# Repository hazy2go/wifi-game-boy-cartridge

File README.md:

# WiFi Game Boy Cartridge (Rev B)

A WiFi cartridge for the original Game Boy and the Game Boy Color that **can't brown out the console**.
An RP2350 serves the whole cartridge bus, and an ESP32-C3 radio sits behind a power stage. That stage limits what the cart takes from the console to a steady 150 mA and never pulls the console's 5 V rail below 4.588 V.
Fully assembled by JLCPCB, nothing to hand-solder. Designed by Hazy, co-created with RemAI.

| | |
|---|---|
| Status (2026-10-16) | Hardware design finished, all checks green, JLC order files ready, **not ordered yet**. Bench tests on a XIAO ESP32C3 dev board are under way: RF calibration (about 30 ms at about 60 mA, looks OK), antenna (strong) and the radio app on real WiFi (all commands work) are done; the Pico 2 link test and a power-model update with the measured numbers come next. See `docs/LOGBOOK.md`. |
| Board | 6 layers, 0.8 mm, standard cartridge shell, USB-C |
| Cartridge core | RP2350B + 8 MB HyperRAM + 16 MB flash + microSD + RTC, serving the cartridge bus over PIO (the proven Croco Cartridge design) |
| Radio | ESP32-C3-MINI-1U on the RP2350's SPI bus, stick-on FPC antenna (MHF III plug) inside the shell. Both chips flash over the one USB-C port (built-in USB hub) |
| Power | USB/console power mux → 150 mA current limit → precision input-voltage regulator (console never pulled below 4.588 V ±1 %) → ~1 mF reservoir → power-good → buck-boost to 3.3 V. The radio firmware admits every WiFi frame against the energy left in the reservoir |

## Why

Earlier WiFi carts powered the radio straight from the Game Boy's 5 V. Every transmit burst (170 to 350 mA) hit the console's weak power converter, and on tired batteries the whole system collapsed.
Here the console only ever sees a steady, limited draw. The bursts come out of a local reservoir, and if the console can't keep up, the radio waits instead of the Game Boy crashing.

| Top | Bottom |
|---|---|
|  |  |

## Proven before ordering

None of this has been built yet. Instead, everything was simulated against real part models and checked against the actual layout:
- **Power stage, at transistor level:** ngspice with TI and Vishay vendor models, covering hot-plug, bursts after idle, loop stability and every tolerance corner (`sim/power`, audits A1 to A8).
- **Full system:** a real Game Boy ROM runs in a cycle-accurate emulator and goes through the cartridge's mailbox. The models cover the RP2350, the ESP32-C3 running the *shipped* power-manager C code, and the power plant including the routed copper's resistance. Tested on fresh, tired and weak batteries (`sim/system`).
- **Layout:**
  - KiCad ERC, DRC and connectivity are clean against the Croco baseline (`verify/`).
  - Every part is checked pin by pin against the exact JLC part.
  - The placement file is derived from JLC's own footprints.

Demo ROM in that simulation: WiFi scan (real networks seen by the host), password entry, then a live BTC/USD chart:

## Repository

| Path | What |
|---|---|
| `CLAUDE.md` | Handoff: current status, rules, software to-do (start here) |
| `docs/ARCHITECTURE.md` | Block diagram, why each block, pin budget |
| `docs/LOGBOOK.md` | Every decision, check and result, in order |
| `hw/rev-b/` | KiCad project, layout tools, `fab/` order files (`fab/ORDER.md`) |
| `docs/ROM_DEV.md` | **Building ROMs for the cart:** mailbox, commands, timing, testing |
| `gb/gbdk/`, `gb/rgbds/` | WiFi libraries for C (GBDK-2020) and assembly (RGBDS), template, examples |
| `firmware/esp32c3/` | Radio firmware: app, power manager, link protocol, shared C components |
| `firmware/xiao/` | Bench tests for the dev board (calibration time, antenna, boot time) |
| `sim/power/`, `sim/system/` | Power-stage and full-system simulations (`run_rom.py` runs any ROM on the simulated cart) |
| `verify/` | Pre-order gates |
| `legacy/` | The original ESP8266 cartridge's code, PCB and shell, kept for reference only |

## Credits

- Designed by [hazy2go](https://github.com/hazy2go), co-created with RemAI (the avatar on the back of the board).
- Forked from [Staacks/wifi-game-boy-cartridge](https://github.com/Staacks/wifi-game-boy-cartridge) (there.oughta.be). The original ESP8266 cartridge was the idea and the starting point.
- The cartridge core is [Croco Cartridge V2.1](https://github.com/shilga/rp-gameboy-cartridge-hw) by shilga. Firmware base: [rp2350-gameboy-cartridge-firmware](https://github.com/shilga/rp2350-gameboy-cartridge-firmware).
- The emulator in the simulation is [Peanut-GB](https://github.com/deltabeard/Peanut-GB). The DMG power-supply analysis uses [Gekkio's gb-schematics](https://github.com/Gekkio/gb-schematics).

## License

| What | License |
|---|---|
| Hardware design (`hw/rev-b/`: schematic, board, fab files) | CERN-OHL-P v2, inherited from Croco Cartridge (`hw/rev-b/LICENSE-CERN-OHL-P.md`) |
| Everything else here: radio firmware (`firmware/`), Game Boy libraries and examples (`gb/`), simulators (`sim/`), gates (`verify/`), board tools (`hw/rev-b/tools/`), docs | **MIT** (`LICENSE`). Permissive on purpose: ROMs built with the libraries can use any license |
| RP2350 cart firmware ([hazy2go/rp2350-gameboy-cartridge-firmware](https://github.com/hazy2go/rp2350-gameboy-cartridge-firmware)) | GPL-3, as its upstream (Croco) |
| `sim/system/third_party/Peanut-GB` | MIT (one local fix, marked in the code) |
| `sim/system/rom/font8x8_basic.h` (test ROM font) | Public domain (Daniel Hepper, after the IBM VGA font) |
| Vendor SPICE models (TI, Vishay) | Not included: `sim/models/fetch_models.py` downloads them under the vendors' terms |
| `legacy/` | The original project's licenses: GPL-3 for code and PCB, CC-BY-NC-SA for the shell (`legacy/README.md`) |

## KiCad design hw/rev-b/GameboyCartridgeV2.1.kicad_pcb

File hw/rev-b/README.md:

# Rev B hardware

Status (2026-10-14): 6-layer 0.8 mm, all parts placed, fully routed and tidied, all gates green (see below). Not ordered yet.

Base: **Croco Cartridge V2.1** by shilga, imported unmodified from
https://github.com/shilga/rp-gameboy-cartridge-hw (`KiCad/V2/GameboyCartridgeV2.1`, commit cb750a1, 2025-11-29).
Licence of the imported design: CERN Open Hardware Licence v2 Permissive (`LICENSE-CERN-OHL-P.md`). All credit for the cartridge core goes to the Croco project.

This fork adds a WiFi radio (ESP32-C3) and a console-safe power stage on top of it. See `../../docs/ARCHITECTURE.md` and `../../docs/LOGBOOK.md`.

Rules for changes here:
- The first commit of this folder is the untouched upstream design, so every later diff is ours.
- Nothing is ordered until ERC/DRC are clean against an explicit JLC rule set, the power stage passes `sim/power`, the height/antenna checks in the logbook are closed, and the full-system simulation with a Game Boy ROM (`sim/system`) passes on the final layout. State 2026-10-14: all met; the order files still need Hazy's review.
- Gate commands: `python3 verify/kicad_check.py` (ERC/DRC/unconnected/parity vs Croco's baseline), `verify/jlc_check.py` (DRC at JLC's 6-layer limits), `verify/netlist_check.py`, `verify/sim_vs_netlist.py`, `verify/design_calcs.py`, `sim/system/run_system.py`, `sim/system/run_demo.py`.
- Layout tools used: `tools/` (placement, Freerouting import, finisher, pull-tight cleaner, audits, copper-resistance extraction). Each is documented at the top of the file.
- Croco's author recommends 0.8mm board thickness and ENIG finish.

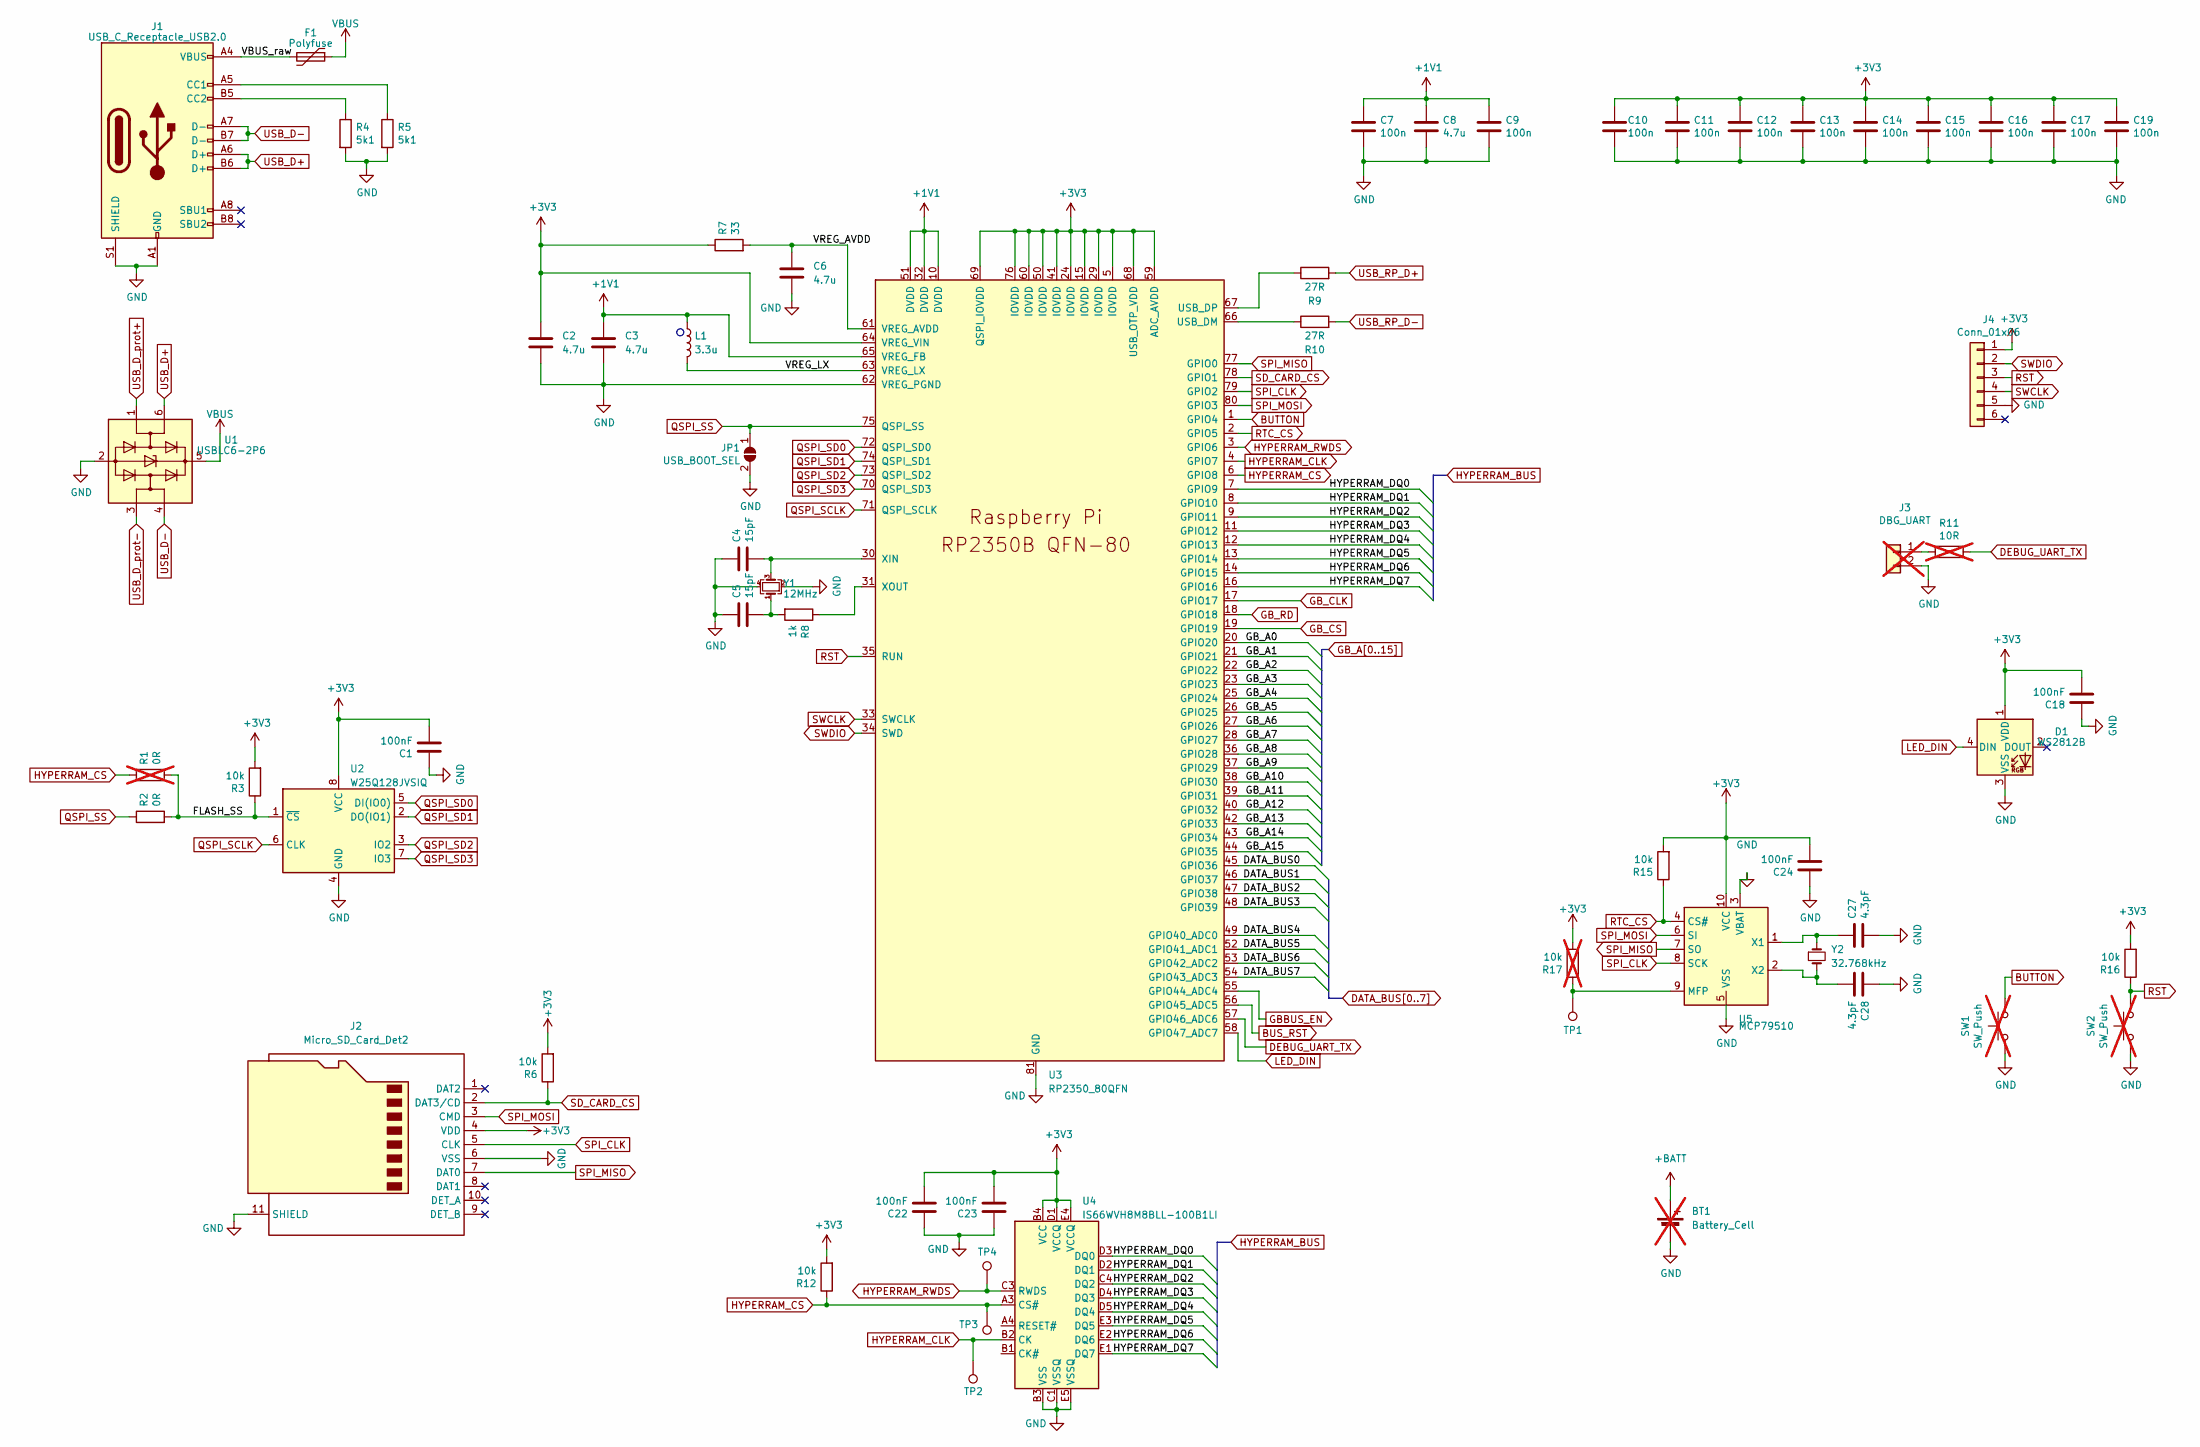
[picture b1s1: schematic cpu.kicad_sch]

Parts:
BT1: Battery_Cell; BatteryHolder_Keystone_3000_1x12mm; LCSC C6997853; not fitted
C1, C18, C22, C23, C24: 100nF; C_0603_1608Metric
C2, C3: 4.7u; C_0402_1005Metric_small_pads
C4, C5: 15pF; C_0603_1608Metric; LCSC C1644
C6, C8: 4.7u; C_0402_1005Metric
C7, C9, C10, C11, C12, C13, C14, C15, C16, C17, C19: 100n; C_0402_1005Metric
C27, C28: 4.3pF; C_0603_1608Metric; LCSC C59526
D1: WS2812B; LED_WS2812B_PLCC4_5.0x5.0mm_P3.2mm; LCSC C2761795
F1: Polyfuse; Fuse_1206_3216Metric; LCSC C2649911
J1: USB_C_Receptacle_USB2.0; USB_C_Receptacle_GCT_USB4105-xx-A_16P_TopMnt_Horizontal; LCSC C2927037
J2: Micro_SD_Card_Det2; microSD_HC_Hirose_DM3D-SF; LCSC C719027
J3: DBG_UART; PinHeader_1x02_P2.54mm_Horizontal; not fitted
J4: Conn_01x06; Tag-Connect_TC2030-IDC-NL_2x03_P1.27mm_Vertical
JP1: USB_BOOT_SEL; SolderJumper-2_P1.3mm_Open_RoundedPad1.0x1.5mm
L1: 3.3u; L_pol_2016; LCSC C42411119
R1: 0R; R_0603_1608Metric; not fitted
R2: 0R; R_0603_1608Metric
R3, R6, R12, R15, R16: 10k; R_0603_1608Metric
R4, R5: 5k1; R_0603_1608Metric
R7: 33; R_0402_1005Metric
R8: 1k; R_0603_1608Metric
R9, R10: 27R; R_0603_1608Metric
R11: 10R; R_0603_1608Metric; not fitted
R17: 10k; R_0603_1608Metric; not fitted
SW1: SW_Push; GameBoy_soft_button; not fitted
SW2: SW_Push; SW_SPST_PTS810; not fitted
TP1, TP2, TP3, TP4: TestPoint; TestPoint_Pad_D1.0mm
U1: USBLC6-2P6; SOT-666; LCSC C2827693
U2: W25Q128JVSIQ; SOIC-8_5.23x5.23mm_P1.27mm; LCSC C97521
U3: RP2350_80QFN; RP2350-QFN-80-1EP_10x10_P0.4mm_EP3.4x3.4mm_ThermalVias; LCSC C42415655
U4: IS66WVH8M8BLL-100B1LI; BGA25C100P5X5_800X600X120N; LCSC C1349096
U5: MCP79510; MSOP-10_3x3mm_P0.5mm; LCSC C627708
Y1: 12MHz; Crystal_SMD_TXC_7M-4Pin_3.2x2.5mm; LCSC C20625731
Y2: 32.768kHz; Crystal_SMD_TXC_9HT11-2Pin_2.0x1.2mm; LCSC C97602

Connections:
+1V1: C3.1, C7.1, C8.1, C9.1, L1.1, U3.10 (DVDD), U3.32 (DVDD), U3.51 (DVDD), U3.65 (VREG_FB)
+3V3: C1.2, C2.1, C10.1, C11.1, C12.1, C13.1, C14.1, C15.1, C16.1, C17.1, C18.2, C19.1, C22.2, C23.2, C24.2, D1.1 (VDD), J2.4 (VDD), J4.1, R3.2, R6.2, R7.1, R12.2, R15.2, R16.2, R17.2, U2.8 (VCC), U3.5 (IOVDD), U3.15 (IOVDD), U3.24 (IOVDD), U3.29 (IOVDD), U3.41 (IOVDD), U3.50 (IOVDD), U3.59 (ADC_AVDD), U3.60 (IOVDD), U3.64 (VREG_VIN), U3.68 (USB_OTP_VDD), U3.69 (QSPI_IOVDD), U3.76 (IOVDD), U4.B4 (VCC), U4.D1 (VCCQ), U4.E4 (VCCQ), U5.10 (VCC); also elsewhere on the board
/CPU/FLASH_SS: R1.2, R2.2, R3.1, U2.1 (~CS)
/CPU/HYPERRAM_DQ0: U3.7 (GPIO9), U4.D3 (DQ0)
/CPU/HYPERRAM_DQ1: U3.8 (GPIO10), U4.D2 (DQ1)
/CPU/HYPERRAM_DQ2: U3.9 (GPIO11), U4.C4 (DQ2)
/CPU/HYPERRAM_DQ3: U3.11 (GPIO12), U4.D4 (DQ3)
/CPU/HYPERRAM_DQ4: U3.12 (GPIO13), U4.D5 (DQ4)
/CPU/HYPERRAM_DQ5: U3.13 (GPIO14), U4.E3 (DQ5)
/CPU/HYPERRAM_DQ6: U3.14 (GPIO15), U4.E2 (DQ6)
/CPU/HYPERRAM_DQ7: U3.16 (GPIO16), U4.E1 (DQ7)
/CPU/VBUS_raw: F1.2, J1.A4 (VBUS), J1.A9 (VBUS), J1.B4 (VBUS), J1.B9 (VBUS)
/CPU/VREG_AVDD: C6.1, R7.2, U3.61 (VREG_AVDD)
/CPU/VREG_LX: L1.2, U3.63 (VREG_LX)
BUS_RST: U3.56 (GPIO45_ADC5); also elsewhere on the board
BUTTON: SW1.1, U3.1 (GPIO4)
DATA_BUS0: U3.45 (GPIO36); also elsewhere on the board
DATA_BUS1: U3.46 (GPIO37); also elsewhere on the board
DATA_BUS2: U3.47 (GPIO38); also elsewhere on the board
DATA_BUS3: U3.48 (GPIO39); also elsewhere on the board
DATA_BUS4: U3.49 (GPIO40_ADC0); also elsewhere on the board
DATA_BUS5: U3.52 (GPIO41_ADC1); also elsewhere on the board
DATA_BUS6: U3.53 (GPIO42_ADC2); also elsewhere on the board
DATA_BUS7: U3.54 (GPIO43_ADC3); also elsewhere on the board
DEBUG_UART_TX: R11.1, U3.57 (GPIO46_ADC6); also elsewhere on the board
GBBUS_EN: U3.55 (GPIO44_ADC4); also elsewhere on the board
GB_A0: U3.20 (GPIO20); also elsewhere on the board
GB_A1: U3.21 (GPIO21); also elsewhere on the board
GB_A2: U3.22 (GPIO22); also elsewhere on the board
GB_A3: U3.23 (GPIO23); also elsewhere on the board
GB_A4: U3.25 (GPIO24); also elsewhere on the board
GB_A5: U3.26 (GPIO25); also elsewhere on the board
GB_A6: U3.27 (GPIO26); also elsewhere on the board
GB_A7: U3.28 (GPIO27); also elsewhere on the board
GB_A8: U3.36 (GPIO28); also elsewhere on the board
GB_A9: U3.37 (GPIO29); also elsewhere on the board
GB_A10: U3.38 (GPIO30); also elsewhere on the board
GB_A11: U3.39 (GPIO31); also elsewhere on the board
GB_A12: U3.40 (GPIO32); also elsewhere on the board
GB_A13: U3.42 (GPIO33); also elsewhere on the board
GB_A14: U3.43 (GPIO34); also elsewhere on the board
GB_A15: U3.44 (GPIO35); also elsewhere on the board
GB_CLK: U3.17 (GPIO17); also elsewhere on the board
GB_CS: U3.19 (GPIO19); also elsewhere on the board
GB_RD: U3.18 (GPIO18); also elsewhere on the board
GND: BT1.2 (-), C1.1, C2.2, C3.2, C4.1, C5.1, C6.2, C7.2, C8.2, C9.2, C10.2, C11.2, C12.2, C13.2, C14.2, C15.2, C16.2, C17.2, C18.1, C19.2, C22.1, C23.1, C24.1, C27.2, C28.1, D1.3 (VSS), J1.A1 (GND), J1.A12 (GND), J1.B1 (GND), J1.B12 (GND), J1.S1 (SHIELD), J2.6 (VSS), J2.11 (SHIELD), J3.2, J4.5, JP1.2 (B), R4.2, R5.2, SW1.2, SW2.2, U1.2 (GND), U2.4 (GND), U3.62 (VREG_PGND), U3.81 (GND), U4.B3 (VSS), U4.C1 (VSSQ), U4.E5 (VSSQ), U5.3 (VBAT), U5.5 (VSS), Y1.2, Y1.4; also elsewhere on the board
HYPERRAM_CLK: TP2.1, U3.4 (GPIO7), U4.B2 (CK)
HYPERRAM_CS: R1.1, R12.1, TP3.1, U3.6 (GPIO8), U4.A3 (CS#)
HYPERRAM_RWDS: TP4.1, U3.3 (GPIO6), U4.C3 (RWDS)
LED_DIN: D1.4 (DIN), U3.58 (GPIO47_ADC7)
unnamed: C5.2, R8.2, Y1.1
unnamed: J1.A5 (CC1), R5.1
unnamed: J1.B5 (CC2), R4.1
unnamed: J3.1, R11.2
unnamed: R10.1, U3.66 (USB_DM)
unnamed: R9.1, U3.67 (USB_DP)
unnamed: C4.2, U3.30 (XIN), Y1.3
unnamed: R8.1, U3.31 (XOUT)
unnamed: R17.1, TP1.1, U5.9 (MFP)
unnamed: C27.1, U5.1 (X1), Y2.1
unnamed: C28.2, U5.2 (X2), Y2.2
QSPI_SCLK: U2.6 (CLK), U3.71 (QSPI_SCLK)
QSPI_SD0: U2.5 (DI(IO0)), U3.72 (QSPI_SD0)
QSPI_SD1: U2.2 (DO(IO1)), U3.74 (QSPI_SD1)
QSPI_SD2: U2.3 (IO2), U3.73 (QSPI_SD2)
QSPI_SD3: U2.7 (IO3), U3.70 (QSPI_SD3)
QSPI_SS: JP1.1 (A), R2.1, U3.75 (QSPI_SS)
RST: J4.3, R16.1, SW2.1, U3.35 (RUN)
RTC_CS: R15.1, U3.2 (GPIO5), U5.4 (CS#)
SD_CARD_CS: J2.2 (DAT3/CD), R6.1, U3.78 (GPIO1)
SPI_CLK: J2.5 (CLK), U3.79 (GPIO2), U5.8 (SCK); also elsewhere on the board
SPI_MISO: J2.7 (DAT0), U3.77 (GPIO0), U5.7 (SO); also elsewhere on the board
SPI_MOSI: J2.3 (CMD), U3.80 (GPIO3), U5.6 (SI); also elsewhere on the board
SWCLK: J4.4, U3.33 (SWCLK)
SWDIO: J4.2, U3.34 (SWD)
USB_D+: J1.A6 (D+), J1.B6 (D+), U1.6 (I/O1)
USB_D-: J1.A7 (D-), J1.B7 (D-), U1.4 (I/O2)
USB_D_prot+: U1.1 (I/O1); also elsewhere on the board
USB_D_prot-: U1.3 (I/O2); also elsewhere on the board
USB_RP_D+: R9.2; also elsewhere on the board
USB_RP_D-: R10.2; also elsewhere on the board
VBUS: F1.1, U1.5 (VBUS); also elsewhere on the board

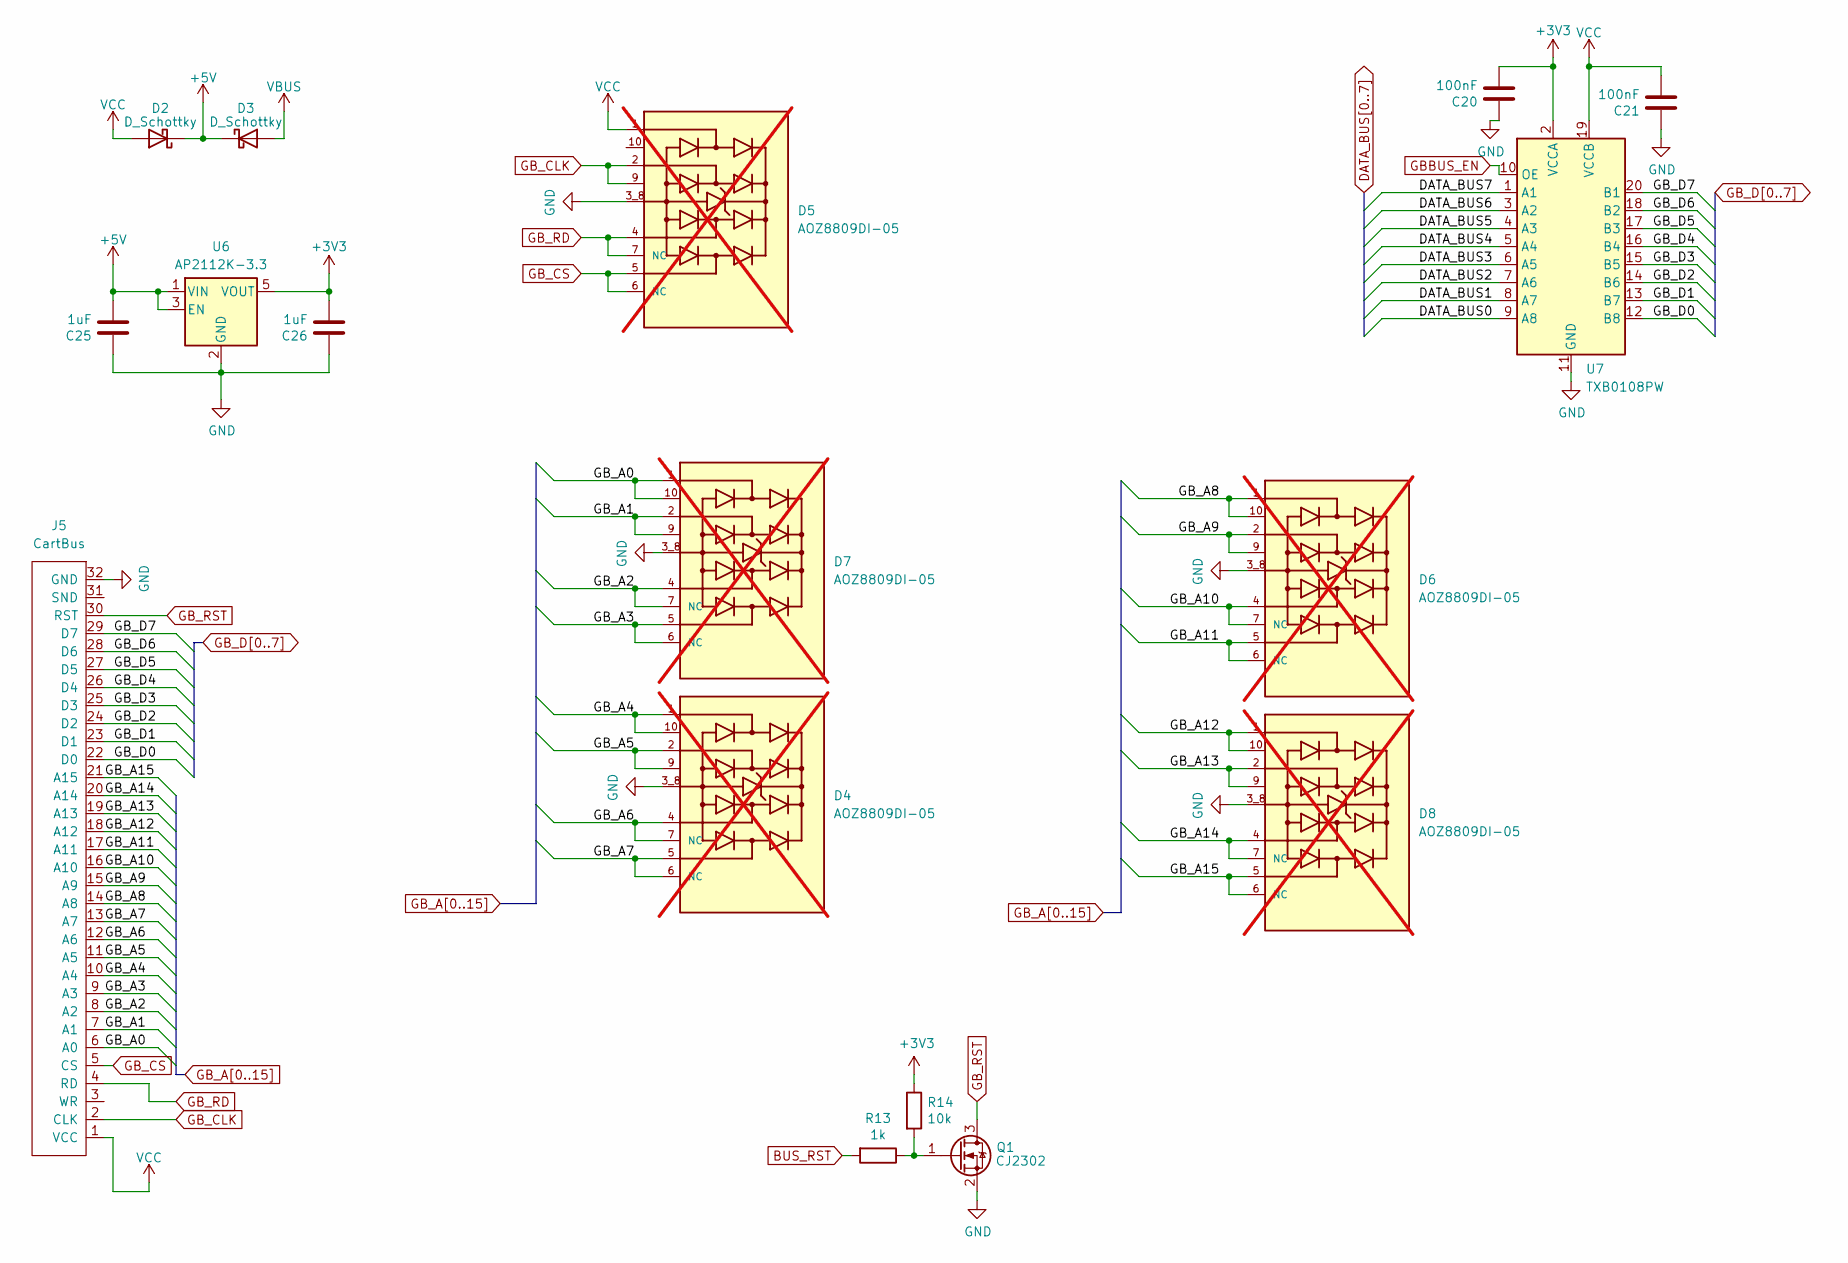
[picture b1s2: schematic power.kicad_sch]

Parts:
C20, C21: 100nF; C_0603_1608Metric
C25, C26: 1uF; C_0603_1608Metric
D2, D3: D_Schottky; D_SOD-123F; LCSC C669022
D4, D5, D6, D7, D8: AOZ8809DI-05; TVS_AOZ8809DI-05; PARTREV Rev. 7.0; not fitted
J5: CartBus; GameBoy_Cartridge_EdgeConnector
Q1: CJ2302; SOT-23; LCSC C8548
R13: 1k; R_0603_1608Metric
R14: 10k; R_0603_1608Metric
U6: AP2112K-3.3; SOT-23-5; LCSC C51118
U7: TXB0108PW; TSSOP-20_4.4x6.5mm_P0.65mm; LCSC C53406

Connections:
+3V3: C20.2, C26.2, R14.1, U6.5 (VOUT), U7.2 (VCCA); also elsewhere on the board
+5V: C25.2, D2.1 (K), D3.1 (K), U6.1 (VIN), U6.3 (EN)
BUS_RST: R13.2; also elsewhere on the board
DATA_BUS0: U7.9 (A8); also elsewhere on the board
DATA_BUS1: U7.8 (A7); also elsewhere on the board
DATA_BUS2: U7.7 (A6); also elsewhere on the board
DATA_BUS3: U7.6 (A5); also elsewhere on the board
DATA_BUS4: U7.5 (A4); also elsewhere on the board
DATA_BUS5: U7.4 (A3); also elsewhere on the board
DATA_BUS6: U7.3 (A2); also elsewhere on the board
DATA_BUS7: U7.1 (A1); also elsewhere on the board
GBBUS_EN: U7.10 (OE); also elsewhere on the board
GB_A0: D7.1, D7.10, J5.6 (A0); also elsewhere on the board
GB_A1: D7.2, D7.9, J5.7 (A1); also elsewhere on the board
GB_A2: D7.4, D7.7 (NC), J5.8 (A2); also elsewhere on the board
GB_A3: D7.5, D7.6 (NC), J5.9 (A3); also elsewhere on the board
GB_A4: D4.1, D4.10, J5.10 (A4); also elsewhere on the board
GB_A5: D4.2, D4.9, J5.11 (A5); also elsewhere on the board
GB_A6: D4.4, D4.7 (NC), J5.12 (A6); also elsewhere on the board
GB_A7: D4.5, D4.6 (NC), J5.13 (A7); also elsewhere on the board
GB_A8: D6.1, D6.10, J5.14 (A8); also elsewhere on the board
GB_A9: D6.2, D6.9, J5.15 (A9); also elsewhere on the board
GB_A10: D6.4, D6.7 (NC), J5.16 (A10); also elsewhere on the board
GB_A11: D6.5, D6.6 (NC), J5.17 (A11); also elsewhere on the board
GB_A12: D8.1, D8.10, J5.18 (A12); also elsewhere on the board
GB_A13: D8.2, D8.9, J5.19 (A13); also elsewhere on the board
GB_A14: D8.4, D8.7 (NC), J5.20 (A14); also elsewhere on the board
GB_A15: D8.5, D8.6 (NC), J5.21 (A15); also elsewhere on the board
GB_CLK: D5.2, D5.9, J5.2 (CLK~); also elsewhere on the board
GB_CS: D5.5, D5.6 (NC), J5.5 (CS); also elsewhere on the board
GB_D0: J5.22 (D0), U7.12 (B8)
GB_D1: J5.23 (D1), U7.13 (B7)
GB_D2: J5.24 (D2), U7.14 (B6)
GB_D3: J5.25 (D3), U7.15 (B5)
GB_D4: J5.26 (D4), U7.16 (B4)
GB_D5: J5.27 (D5), U7.17 (B3)
GB_D6: J5.28 (D6), U7.18 (B2)
GB_D7: J5.29 (D7), U7.20 (B1)
GB_RD: D5.4, D5.7 (NC), J5.4 (RD); also elsewhere on the board
GB_RST: J5.30 (RST), Q1.3 (D)
GND: C20.1, C21.1, C25.1, C26.1, D4.3_8, D5.3_8, D6.3_8, D7.3_8, D8.3_8, J5.32 (GND), Q1.2 (S), U6.2 (GND), U7.11 (GND); also elsewhere on the board
unnamed: Q1.1 (G), R13.1, R14.2
VBUS: D3.2 (A); also elsewhere on the board
VCC: C21.2, D2.2 (A), D5.1, J5.1 (VCC), U7.19 (VCCB); also elsewhere on the board
